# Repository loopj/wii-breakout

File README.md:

# Wii Motherboard Breakout PCB

Wii motherboard breakout board for USB, Bluetooth, GameCube controllers, A/V, and RST lines.

This is designed to be permanently mounted to a (trimmed) Wii motherboard to give access to peripheral data lines without having to worry about breaking small wires. I designed this allow me to rapidly prototype "daughterboard" peripheral PCBs without having to de-solder/re-solder.

Useful for prototyping, or for permanent installation on Wii projects which are mounted with the CPU/GPU facing up (probably not most portables).

## Features
- Pads aim to be as close to onboard vias as possible
- Designed to lay flush with 4-layer Wii motherboards
- Cutout for capacitor (C56)
- Can be screw mounted (M2 or M2.5 screws), glued, or soldered
- Castellated mounting holes
- Footprints for vertical JST-SH headers
- Breaks out:
    - USB (D-, D+)
    - Audio (L, R, GND)
    - Component/RGB Video (Y, Pb, Pr, GND)
    - Bluetooth (D1, D2)
    - GameCube Controllers x4 (SI line)
    - Reset Line

## Gerber Files

See [releases](https://github.com/loopj/wii-breakout/releases).

## Order from OSH Park

https://oshpark.com/shared_projects/xyI6Kvkf

## Photos
### Board photo

### Motherboard placement

## PCB renders
### Front

### Back

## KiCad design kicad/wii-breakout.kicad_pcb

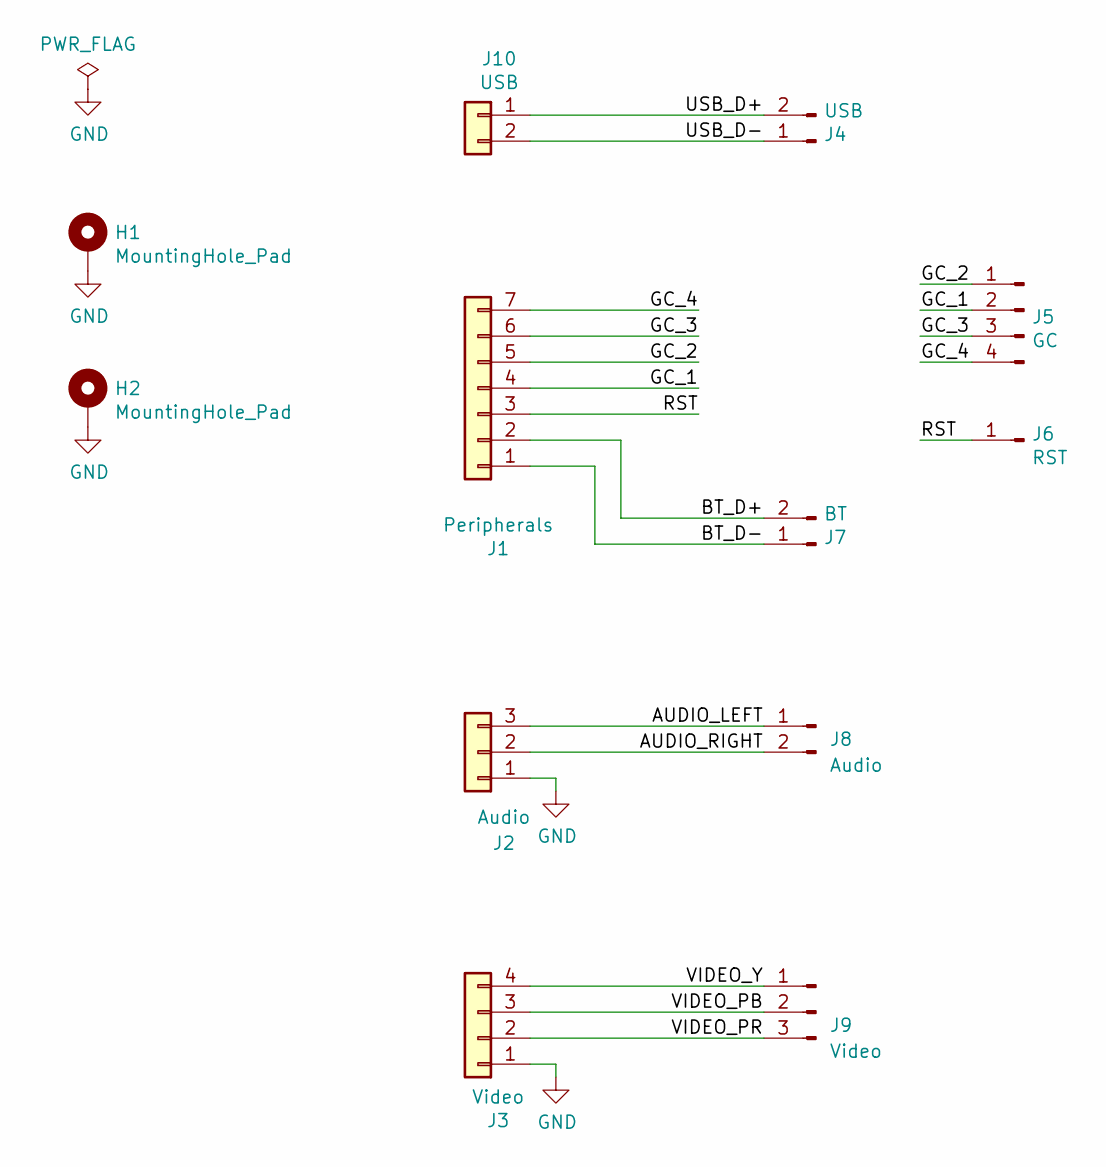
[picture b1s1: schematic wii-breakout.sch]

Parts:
H1, H2: MountingHole_Pad; MountingHole_2.7mm_M2.5_ISO14580_Pad
J1: Peripherals; JST_SH_BM07B-SRSS-TB_1x07-1MP_P1.00mm_Vertical; MPN BM09B-SRSS-TB(LF)(SN)
J2: Audio; JST_SH_BM03B-SRSS-TB_1x03-1MP_P1.00mm_Vertical; MPN BM03B-SRSS-TB(LF)(SN)
J3: Video; JST_SH_BM04B-SRSS-TB_1x04-1MP_P1.00mm_Vertical; MPN BM04B-SRSS-TB(LF)(SN)
J4: USB; TestPoint_2Pads_2.0x1.0mm
J5: GC; TestPoint_4Pads_2.0x1.0mm
J6: RST; TestPoint_Pad_2.0x1.0mm
J7: BT; TestPoint_2Pads_2.0x1.0mm
J8: Audio; TestPoint_2Pads_2.0x1.0mm
J9: Video; TestPoint_3Pads_2.0x1.0mm
J10: USB; JST_SH_BM02B-SRSS-TB_1x02-1MP_P1.00mm_Vertical

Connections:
/AUDIO_LEFT: J2.3, J8.1
/AUDIO_RIGHT: J2.2, J8.2
/BT_D+: J1.2, J7.2
/BT_D-: J1.1, J7.1
/GC_1: J1.4, J5.2
/GC_2: J1.5, J5.1
/GC_3: J1.6, J5.3
/GC_4: J1.7, J5.4
/RST: J1.3, J6.1
/USB_D+: J4.2, J10.1
/USB_D-: J4.1, J10.2
/VIDEO_PB: J3.3, J9.2
/VIDEO_PR: J3.2, J9.3
/VIDEO_Y: J3.4, J9.1
GND: H1.1, H2.1, J2.1, J3.1

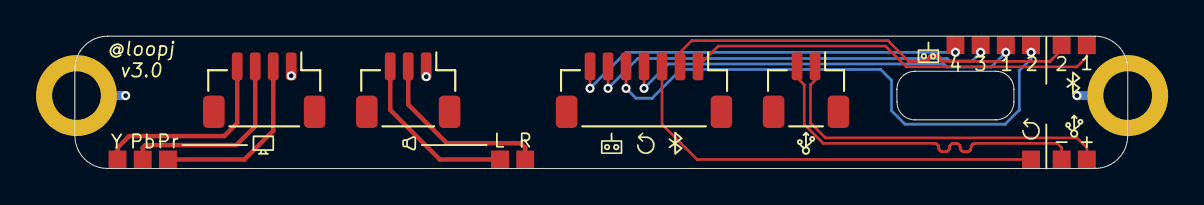
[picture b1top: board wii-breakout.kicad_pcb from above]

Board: 2 copper layers, 58.5 x 7.4 mm, 12 parts (0 on the bottom side), 15 nets.

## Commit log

2020-03-14 v1.0
2020-03-26 Shrink the board
2020-03-31 v2.0
2020-04-11 Include mobo power on breakout
2020-06-16 v3.0 - minimal size, cutout for mobo cap, split USB from data header, reorder GC lines to match mobo
2020-06-16 Readme
